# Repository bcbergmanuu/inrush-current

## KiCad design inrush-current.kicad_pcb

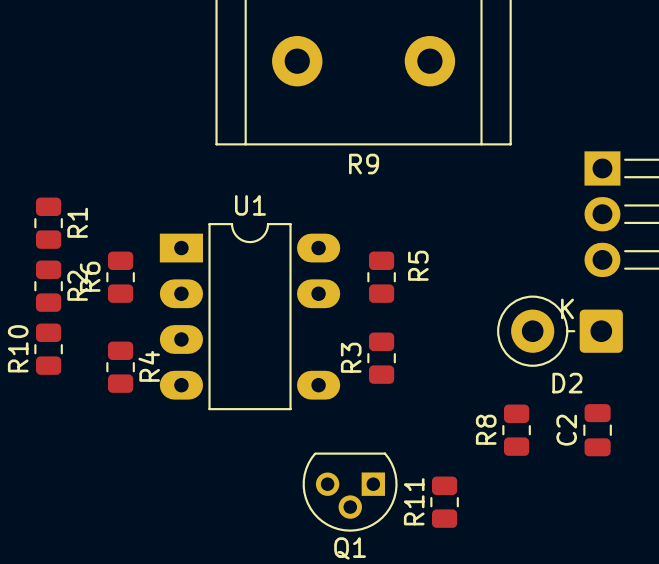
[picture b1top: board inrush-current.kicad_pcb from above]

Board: 2 copper layers, 15 parts (0 on the bottom side), 9 nets, no tracks yet.

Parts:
C2: 10n; C_0805_2012Metric
D2: D_Zener; D_DO-15_P3.81mm_Vertical_KathodeUp
Q1: NMOS; TO-92L
Q2: PMOS; TO-220-3_Horizontal_TabDown
R1: 150K; R_0805_2012Metric
R2: 8K; R_0805_2012Metric
R3: 22k; R_0805_2012Metric
R4, R11: 10k; R_0805_2012Metric
R5: 1k; R_0805_2012Metric
R6, R8, R10: 47k; R_0805_2012Metric
R9: 4; R_Radial_Power_L16.1mm_W9.0mm_P7.37mm
U1: LM311; PowerIntegrations_PDIP-8B

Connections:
0: Q1.3 (S), R2.2, R4.2, R10.2, U1.1 (GND), U1.4 (V-)
+48V: Q2.2 (D), R1.1, R9.1
/Vgate: C2.2, D2.2 (A), Q2.1 (G), R8.2, R11.1
/in+: R3.2, R4.1, U1.3 (-)
/in-: R1.2, R2.1, R6.1, U1.2 (+)
/out: Q1.2 (G), R5.2, R6.2, R10.1, U1.7
unnamed: C2.1, D2.1 (K), Q2.3 (S), R8.1, R9.2
unnamed: Q1.1 (D), R11.2
unnamed: R3.1, R5.1, U1.8 (V+)
